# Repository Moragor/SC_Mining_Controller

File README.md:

# Star Citizen Mining Controller
A handheld mining controller for Star Citizen

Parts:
Arduino Pro Micro: https://www.aliexpress.com/item/32768308647.html

Switches: ON-ON 3-Pin https://www.aliexpress.com/item/4000598302546.html

Power Button: 19mm https://www.aliexpress.com/item/1005003151279874.html?gatewayAdapt=glo2deu

E-Stop: 19mm 3-Pin https://www.aliexpress.com/item/1005003736504591.html?gatewayAdapt=glo2deu

Module Buttons: https://www.aliexpress.com/item/32667944879.html?gatewayAdapt=glo2deu

Slide Potentiometer: ALPS 401547 (RS60112-LIN10K) + ALPS 76561 (KNOPF 4X1,2RT)

Joystick: APEM 3150RAK600

Switch rubber grommets: APEM U598

Front Panel: Order from https://www.schaeffer-ag.de/ (EU) or https://www.frontpanelexpress.com/ (NA)

Demo: https://www.youtube.com/watch?v=b_x-qhPem98

[![CC BY-NC-SA 4.0][cc-by-nc-sa-shield]][cc-by-nc-sa]

[cc-by-nc-sa]: http://creativecommons.org/licenses/by-nc-sa/4.0/
[cc-by-nc-sa-shield]: https://img.shields.io/badge/License-CC%20BY--NC--SA%204.0-lightgrey.svg

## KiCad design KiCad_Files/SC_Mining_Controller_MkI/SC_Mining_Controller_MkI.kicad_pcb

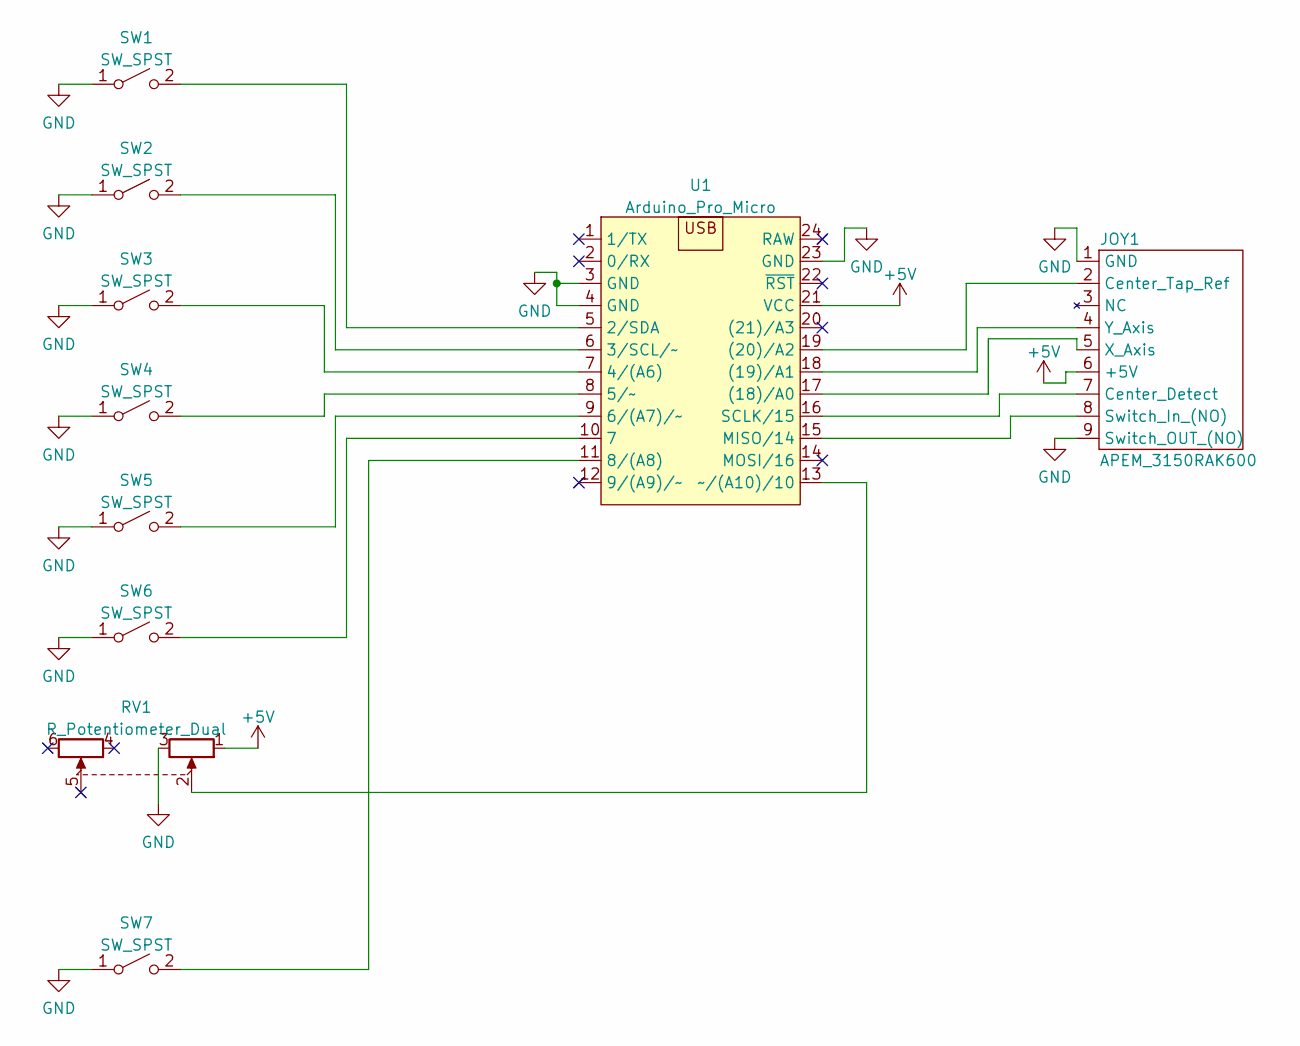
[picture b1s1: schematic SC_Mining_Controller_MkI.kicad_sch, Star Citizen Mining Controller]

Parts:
JOY1: APEM_3150RAK600; Molex_KK-254_AE-6410-09A_1x09_P2.54mm_Vertical
RV1: R_Potentiometer_Dual; Sliding_Potentiometer_RS60112
SW1, SW2, SW3, SW4, SW5, SW6, SW7: SW_SPST; JST_XH_B2B-XH-A_1x02_P2.50mm_Vertical
U1: Arduino_Pro_Micro; ProMicro

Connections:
+5V: JOY1.6 (+5V), RV1.1, U1.21 (VCC)
GND: JOY1.1 (GND), JOY1.9 (Switch_OUT_(NO)), RV1.3, SW1.1 (A), SW2.1 (A), SW3.1 (A), SW4.1 (A), SW5.1 (A), SW6.1 (A), SW7.1 (A), U1.3 (GND), U1.4 (GND), U1.23 (GND)
unnamed: JOY1.2 (Center_Tap_Ref), U1.19 ((20)/A2)
unnamed: JOY1.4 (Y_Axis), U1.18 ((19)/A1)
unnamed: JOY1.5 (X_Axis), U1.17 ((18)/A0)
unnamed: JOY1.7 (Center_Detect), U1.16 (SCLK/15)
unnamed: JOY1.8 (Switch_In_(NO)), U1.15 (MISO/14)
unnamed: RV1.2, U1.13 (~/(A10)/10)
unnamed: SW1.2 (B), U1.5 (2/SDA)
unnamed: SW2.2 (B), U1.6 (3/SCL/~)
unnamed: SW3.2 (B), U1.7 (4/(A6))
unnamed: SW4.2 (B), U1.8 (5/~)
unnamed: SW5.2 (B), U1.9 (6/(A7)/~)
unnamed: SW6.2 (B), U1.10 (7)
unnamed: SW7.2 (B), U1.11 (8/(A8))

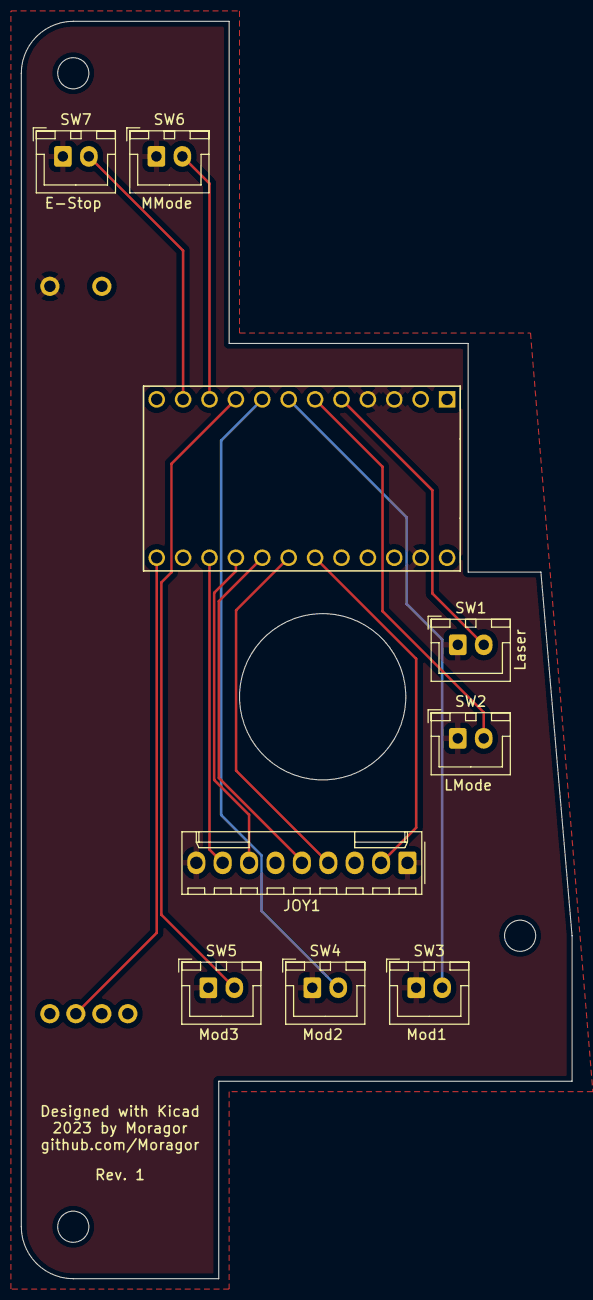
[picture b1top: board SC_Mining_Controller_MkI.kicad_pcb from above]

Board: 2 copper layers, 53.0 x 121.0 mm, 10 parts (1 on the bottom side), 15 nets.

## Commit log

2023-10-29 Initial Upload
2023-10-29 Picture added
2023-10-30 Added front panel file and parts to readme
2023-10-30 Fixed markdown formatting -_-
2024-03-09 Adding pictures and 3D files
2024-06-09 Added joystick library download url
